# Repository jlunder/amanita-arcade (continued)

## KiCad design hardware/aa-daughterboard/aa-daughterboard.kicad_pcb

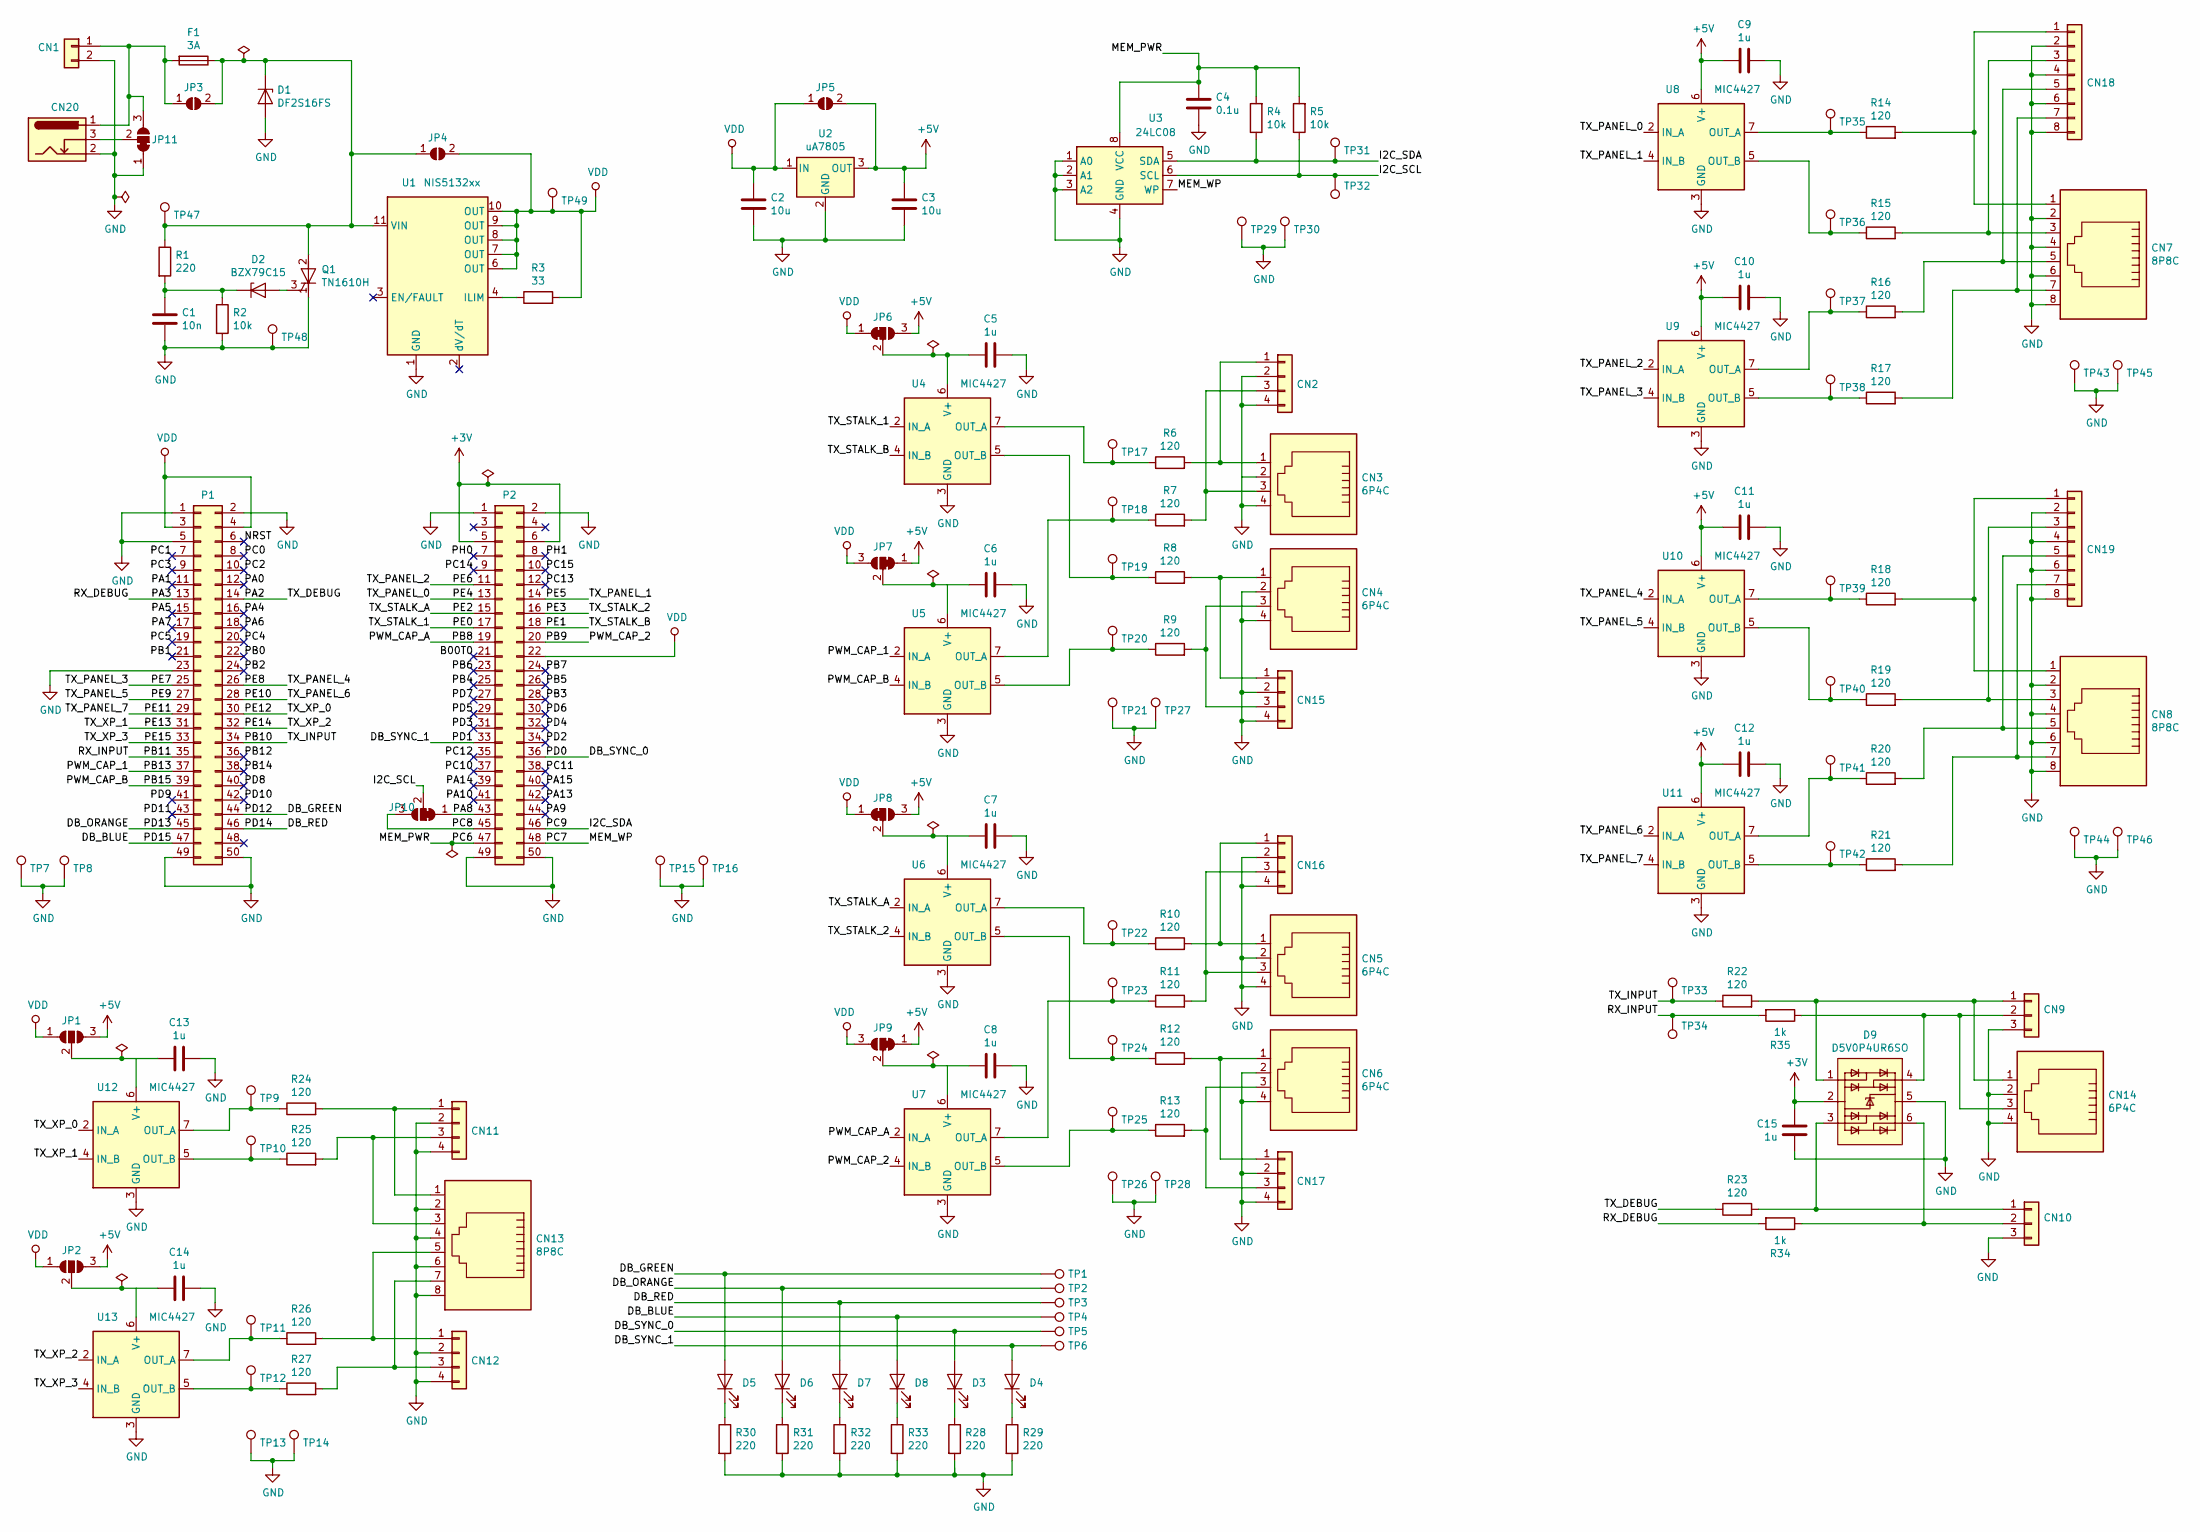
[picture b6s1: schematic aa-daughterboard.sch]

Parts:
C1: 10n; C_0603_1608Metric
C2, C3: 10u; C_0805_2012Metric
C4: 0.1u; C_0603_1608Metric
C5, C6, C7, C8, C9, C10, C11, C12, C13, C14, C15: 1u; C_0805_2012Metric
CN1: Conn_01x02; SolderWirePad_1x02_P7.62mm_Drill2.5mm
CN2, CN11, CN12, CN15, CN16, CN17: Conn_01x04; PinHeader_1x04_P2.54mm_Vertical
CN3, CN4, CN5, CN6, CN14: 6P4C; RJ25_Amphenol_90520
CN7, CN8, CN13: 8P8C; RJ25_Amphenol_69255
CN9, CN10: Conn_01x03; PinHeader_1x03_P2.54mm_Vertical
CN18, CN19: Conn_01x08; PinHeader_1x08_P2.54mm_Vertical
CN20: Barrel_Jack; BarrelJack_Horizontal
D1: DF2S16FS; D_SOD-923
D2: BZX79C15; D_DO-35_SOD27_P7.62mm_Horizontal
D3, D4, D5, D6, D7, D8: LED; LED_0603_1608Metric
D9: D5V0P4UR6SO; SOT-23-6
F1: 3A; Fuseholder_Clip_5x20_Bel_FC-211-22
JP1, JP2: SolderJumper_3_Open; SolderJumper-3_P1.3mm_Open_RoundedPad1.0x1.5mm
JP3, JP4, JP5: SolderJumper_2_Open; SolderJumper-2_P1.3mm_Open_RoundedPad1.0x1.5mm
JP6, JP7, JP8, JP9, JP10, JP11: SolderJumper_3_Bridged12; SolderJumper-3_P1.3mm_Bridged2Bar12_RoundedPad1.0x1.5mm
P1, P2: Conn_02x25_Odd_Even; PinSocket_2x25_P2.54mm_Vertical
Q1: TN1610H; TO-220-3_Horizontal_TabDown
R1, R28, R29, R30, R31, R32, R33: 220; R_0603_1608Metric
R2, R4, R5: 10k; R_0603_1608Metric
R3: 33; R_0603_1608Metric
R6, R7, R8, R9, R10, R11, R12, R13, R14, R15, R16, R17, R18, R19, R20, R21, R24, R25, R26, R27: 120; R_1210_3225Metric
R22, R23: 120; R_0603_1608Metric
R34, R35: 1k; R_0603_1608Metric
TP1, TP2, TP3, TP4, TP5, TP6, TP7, TP8, TP9, TP10, TP11, TP12, TP13, TP14, TP15, TP16, TP17, TP18, TP19, TP20, TP21, TP22, TP23, TP24, TP25, TP26, TP27, TP28, TP29, TP30, TP31, TP32, TP33, TP34, TP35, TP36, TP37, TP38, TP39, TP40, TP41, TP42, TP43, TP44, TP45, TP46, TP47, TP48, TP49: TestPoint; TestPoint_THTPad_D1.0mm_Drill0.5mm
U1: NIS5132xx; DFN-10-1EP_3x3mm_P0.5mm_EP1.75x2.7mm
U2: uA7805; TO-220-3_Vertical
U3: 24LC08; DIP-8_W7.62mm_Socket
U4, U5, U6, U7, U8, U9, U10, U11, U12, U13: MIC4427; SOIC-8-1EP_3.9x4.9mm_P1.27mm_EP2.35x2.35mm

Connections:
+3V: C15.1, D9.2 (A), P2.5, P2.6
+5V: C3.1, C9.1, C10.1, C11.1, C12.1, JP1.3 (B), JP2.3 (B), JP5.2 (B), JP6.3 (B), JP7.1 (A), JP8.3 (B), JP9.1 (A), U2.3 (OUT), U8.6 (V+), U9.6 (V+), U10.6 (V+), U11.6 (V+)
/B00T0: P2.21
/DB_BLUE: D8.2 (A), P1.47, TP4.1
/DB_GREEN: D5.2 (A), P1.44, TP1.1
/DB_ORANGE: D6.2 (A), P1.45, TP2.1
/DB_RED: D7.2 (A), P1.46, TP3.1
/DB_SYNC_0: D3.2 (A), P2.36, TP5.1
/DB_SYNC_1: D4.2 (A), P2.33, TP6.1
/I2C_SCL: JP10.2 (C), R5.1, TP32.1, U3.6 (SCL)
/I2C_SDA: P2.46, R4.1, TP31.1, U3.5 (SDA)
/MEM_PWR: C4.1, P2.47, R4.2, R5.2, U3.8 (VCC)
/MEM_WP: P2.48, U3.7 (WP)
/NRST: P1.6
/PA0: P1.12
/PA1: P1.11
/PA2: P1.14, R23.1
/PA3: P1.13, R34.2
/PA4: P1.16
/PA5: P1.15
/PA6: P1.18
/PA7: P1.17
/PA8: JP10.1 (A), P2.43
/PA9: P2.44
/PA10: P2.41
/PA13: P2.42
/PA14: P2.39
/PA15: P2.40
/PB0: P1.22
/PB1: P1.21
/PB2: P1.24
/PB3: P2.28
/PB4: P2.25
/PB5: P2.26
/PB6: P2.23
/PB7: P2.24
/PB8: P2.19, U7.2 (IN_A)
/PB9: P2.20, U7.4 (IN_B)
/PB10: P1.34, R22.1, TP33.1
/PB11: P1.35, R35.2, TP34.1
/PB12: P1.36
/PB13: P1.37, U5.2 (IN_A)
/PB14: P1.38
/PB15: P1.39, U5.4 (IN_B)
/PC0: P1.8
/PC1: P1.7
/PC2: P1.10
/PC3: P1.9
/PC4: P1.20
/PC5: P1.19
/PC8: JP10.3 (B), P2.45
/PC10: P2.37
/PC11: P2.38
/PC12: P2.35
/PC13: P2.12
/PC14: P2.9
/PC15: P2.10
/PD2: P2.34
/PD3: P2.31
/PD4: P2.32
/PD5: P2.29
/PD6: P2.30
/PD7: P2.27
/PD8: P1.40
/PD9: P1.41
/PD10: P1.42
/PD11: P1.43
/PE0: P2.17, U4.2 (IN_A)
/PE1: P2.18, U4.4 (IN_B)
/PE2: P2.15, U6.2 (IN_A)
/PE3: P2.16, U6.4 (IN_B)
/PE4: P2.13, U8.2 (IN_A)
/PE5: P2.14, U8.4 (IN_B)
/PE6: P2.11, U9.2 (IN_A)
/PE7: P1.25, U9.4 (IN_B)
/PE8: P1.26, U10.2 (IN_A)
/PE9: P1.27, U10.4 (IN_B)
/PE10: P1.28, U11.2 (IN_A)
/PE11: P1.29, U11.4 (IN_B)
/PE12: P1.30, U12.2 (IN_A)
/PE13: P1.31, U12.4 (IN_B)
/PE14: P1.32, U13.2 (IN_A)
/PE15: P1.33, U13.4 (IN_B)
/PH0: P2.7
/PH1: P2.8
GND: C1.2, C2.2, C3.2, C4.2, C5.2, C6.2, C7.2, C8.2, C9.2, C10.2, C11.2, C12.2, C13.2, C14.2, C15.2, CN1.2, CN2.2, CN2.4, CN3.2, CN3.4, CN4.2, CN4.4, CN5.2, CN5.4, CN6.2, CN6.4, CN7.2, CN7.4, CN7.6, CN7.8, CN8.2, CN8.4, CN8.6, CN8.8, CN9.3, CN10.3, CN11.2, CN11.4, CN12.2, CN12.4, CN13.2, CN13.4, CN13.6, CN13.8, CN14.2, CN14.4, CN15.2, CN15.4, CN16.2, CN16.4, CN17.2, CN17.4, CN18.2, CN18.4, CN18.6, CN18.8, CN19.2, CN19.4, CN19.6, CN19.8, CN20.2, D1.2 (A), D9.5 (K), JP11.1 (A), P1.1, P1.2, P1.5, P1.23, P1.49, P1.50, P2.1, P2.2, P2.49, P2.50, Q1.1 (K), R2.2, R28.2, R29.2, R30.2, R31.2, R32.2, R33.2, TP7.1, TP8.1, TP13.1, TP14.1, TP15.1, TP16.1, TP21.1, TP26.1, TP27.1, TP28.1, TP29.1, TP30.1, TP43.1, TP44.1, TP45.1, TP46.1, TP48.1, U1.1 (GND), U2.2 (GND), U3.1 (A0), U3.2 (A1), U3.3 (A2), U3.4 (GND), U4.3 (GND), U5.3 (GND), U6.3 (GND), U7.3 (GND), U8.3 (GND), U9.3 (GND), U10.3 (GND), U11.3 (GND), U12.3 (GND), U13.3 (GND)
unnamed: C1.1, D2.1 (K), R1.2, R2.1
unnamed: C5.1, JP6.2 (C), U4.6 (V+)
unnamed: C6.1, JP7.2 (C), U5.6 (V+)
unnamed: C7.1, JP8.2 (C), U6.6 (V+)
unnamed: C8.1, JP9.2 (C), U7.6 (V+)
unnamed: C13.1, JP1.2 (C), U12.6 (V+)
unnamed: C14.1, JP2.2 (C), U13.6 (V+)
unnamed: CN1.1, CN20.1, F1.2, JP3.1 (A), JP11.3 (B)
unnamed: CN2.1, CN3.1, R6.2
unnamed: CN2.3, CN3.3, R7.2
unnamed: CN10.1, D9.3 (K), R23.2
unnamed: CN10.2, D9.6 (K), R34.1
unnamed: CN11.1, CN13.1, R24.2
unnamed: CN11.3, CN13.3, R25.2
unnamed: CN12.1, CN13.5, R26.2
unnamed: CN12.3, CN13.7, R27.2
unnamed: CN9.1, CN14.1, D9.1 (K), R22.2
unnamed: CN9.2, CN14.3, D9.4 (K), R35.1
unnamed: CN4.1, CN15.1, R8.2
unnamed: CN4.3, CN15.3, R9.2
unnamed: CN5.1, CN16.1, R10.2
unnamed: CN5.3, CN16.3, R11.2
unnamed: CN6.1, CN17.1, R12.2
unnamed: CN6.3, CN17.3, R13.2
unnamed: CN7.1, CN18.1, R14.2
unnamed: CN7.3, CN18.3, R15.2
unnamed: CN7.5, CN18.5, R16.2
unnamed: CN7.7, CN18.7, R17.2
unnamed: CN8.1, CN19.1, R18.2
unnamed: CN8.3, CN19.3, R19.2
unnamed: CN8.5, CN19.5, R20.2
unnamed: CN8.7, CN19.7, R21.2
unnamed: CN20.3, JP11.2 (C)
unnamed: D1.1 (K), F1.1, JP3.2 (B), JP4.1 (A), Q1.2 (A), R1.1, TP47.1, U1.11 (VIN)
unnamed: D2.2 (A), Q1.3 (G)
unnamed: D3.1 (K), R28.1
unnamed: D4.1 (K), R29.1
unnamed: D5.1 (K), R30.1
unnamed: D6.1 (K), R31.1
unnamed: D7.1 (K), R32.1
unnamed: D8.1 (K), R33.1
unnamed: R3.1, U1.4 (ILIM)
unnamed: R6.1, TP17.1, U4.7 (OUT_A)
unnamed: R7.1, TP18.1, U5.7 (OUT_A)
unnamed: R8.1, TP19.1, U4.5 (OUT_B)
unnamed: R9.1, TP20.1, U5.5 (OUT_B)
unnamed: R10.1, TP22.1, U6.7 (OUT_A)
unnamed: R11.1, TP23.1, U7.7 (OUT_A)
unnamed: R12.1, TP24.1, U6.5 (OUT_B)
unnamed: R13.1, TP25.1, U7.5 (OUT_B)
unnamed: R14.1, TP35.1, U8.7 (OUT_A)
unnamed: R15.1, TP36.1, U8.5 (OUT_B)
unnamed: R16.1, TP37.1, U9.7 (OUT_A)
unnamed: R17.1, TP38.1, U9.5 (OUT_B)
unnamed: R18.1, TP39.1, U10.7 (OUT_A)
unnamed: R19.1, TP40.1, U10.5 (OUT_B)
unnamed: R20.1, TP41.1, U11.7 (OUT_A)
unnamed: R21.1, TP42.1, U11.5 (OUT_B)
unnamed: R24.1, TP9.1, U12.7 (OUT_A)
unnamed: R25.1, TP10.1, U12.5 (OUT_B)
unnamed: R26.1, TP11.1, U13.7 (OUT_A)
unnamed: R27.1, TP12.1, U13.5 (OUT_B)
VDD: C2.1, JP1.1 (A), JP2.1 (A), JP4.2 (B), JP5.1 (A), JP6.1 (A), JP7.3 (B), JP8.1 (A), JP9.3 (B), P1.3, P1.4, P2.22, R3.2, TP49.1, U1.6 (OUT), U1.7 (OUT), U1.8 (OUT), U1.9 (OUT), U1.10 (OUT), U2.1 (IN)

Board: 4 copper layers, 156 parts (1 on the bottom side), 102 nets, no tracks yet.

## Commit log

2015-10-15 LED blinky test.
2015-10-17 Some kinda audio output when I don't use DMA?
2015-10-17 DMA circular buffer audio works! Yay
2015-10-17 Audio data
2015-10-17 Heartbeat sound fully working!
2015-10-18 Final for the party!
2016-04-16 Rename to Amanita Arcade, begin refactor/cleanup
2016-05-24 Begin integrating synth stuff from rotterbox
2016-05-24 MPR121 code
2016-06-02 Get touch working with MPR121 sensors
2016-06-04 Sketch out game logic, UART hardware implementation
2016-06-05 Add a couple high frequency timers.
2016-06-07 Add hardware support for WS2811 output via I2S -- fix problem with I2S clock generation (??? I think? How did this ever work with the CS43L22 though?)
2016-06-08 Yay basic output seems to basically work!
2016-06-09 Fix color order in test pattern, bit order in output code
2016-06-11 Refactor code out of ugly giant main.c and into submodules
2016-06-18 Build out skeleton of game and animation/audio code
2016-06-28 Decluttering, start implementing light control
2016-07-01 Add timer support to HW lib, switch to bitbanged LED output.
2016-07-03 Implement first pass light compositing
2016-07-04 Fix cycle play bugs.
2016-07-09 Minor changes to match festival hardware
2017-05-18 Add GitEye .project exclusion
2017-06-23 Add new mbed rewrite of Amanita Arcade. Wish me luck
2017-06-23 Basic skeleton, some utilities here
2017-06-23 First pass input, much framework
2017-06-24 Debug test controller input.
2017-06-25 Implement algorithm to pack light data for output via serial port (!!)
2017-06-25 First working version of WS2812 (serial) drive
2017-06-25 First pass of WS2812 output -- output works, seems stable over long(ish) cable runs.
2017-06-26 Beginning implementation of lights animation framework.
2017-06-27 First crack at new animation system
2017-07-07 Add separate firmware for the controls controller
2017-07-07 Fix pin assignment
2017-07-07 First pass of actual (WS2812) output ordering/encoding
2017-07-07 Rename aa-test-1 to aa-main 'cause it's the real deal now
2017-07-07 Straighten out composite step slightly
2017-07-08 Much bugfixing, implement lights on button press
2017-07-08 Final thing! Implemented game logic.
2017-08-06 Remove old, stale source
2017-08-06 Initial values were causing the controller to think all buttons were held down constantly forever if PS2 controller not plugged in on boot.
2017-08-06 Fix rendering bugs, change gameplay to use the first button press as start of sequence
2018-06-20 Improve efficiency of output() by using work to delay instead of __NOP()
2018-06-20 Add explicit optimization/memory barrier control to output() as future-proofing
2018-06-24 Tweak lights output to show scoreboard at 13% intensity, show actually the output in the buffer rather than a test pattern
2018-07-01 Panel font render test
2018-07-02 Clean up some of the LED output code
2018-07-02 Font, cursor test
2018-07-02 Font gradients, to improve legibility
2018-07-03 Add invert option to font rendering for the cursor
2018-07-03 Add debug background to output code, adjust timing slightly
2018-07-03 Separate color reorder for panel and stalks... that was a confusing color problem
2018-07-04 Refactor pool system, add (ugh) templates to make it easier to add animators
2018-07-07 Refactor a bunch of draw code, implement scrolling text for instructions
2018-07-08 Refactor/rewrite a bunch of stuff! Also implement vis for scoreboard.
2018-07-29 Add VS Code .gitignore, make project work on latest Platform.IO (now it offers mbed upload for STM32F4Discovery which is not helpful)
2018-07-29 Don't mess with the JTAG lines (it was wigging OpenOCD out)
2018-07-29 Make a best effort to output message from asserts that happen during static init
2018-07-29 Cleanup, improve formatting consistency, VS Code Platform.IO stuff
2018-07-29 Improve debug serial on-demand init a little more elegantly so we can log messages/asserts during static init in a general way
2018-07-29 Fix broken uptime(), frame timing code
2018-07-29 Fix copy in comment
2018-07-30 Implement watchdog timer!
2018-07-30 Not sure why vscode decided to change these settings but sure
2018-07-30 Add input via debug_ser, log game state via vis, adjust vis design slightly
2018-08-01 Fix timer bugs, add debug serial input simulation, reimplement game logic with a modular state machine, fix spurious assert in lights
2018-08-04 Tweak glow/press animations
2018-08-06 Fix issues with transitions, make colors brace-initializable, rationalize draw function naming, improve logo texture, tweak viz
2018-08-07 Tweak animations, etc.
2018-08-07 Fix small bug with endgame handling
2018-08-07 Narrow font for readability, tweak animations
2018-08-27 Implement bitbang I2C for EEPROM
2018-10-15 Consolidate source data, organize
2019-01-03 Post-shambs development (used at Lumiere)
2019-04-19 Current LVDS/RS422 project -- pretty much ready for layout
2019-04-20 First run at aa-daughterboard (current loop version), plus WIP
2019-04-22 Rough grouping of components done
2019-04-23 Add STM32 symbols... I don't think I have this right yet
2019-04-23 Name differential pairs, convert inconvenient 1x8 connectors to 2x4
2019-04-23 Clear out autosaves/junk
2019-04-23 Add gitignore to prevent junk from coming back
2019-05-04 Routed, labeling done pending double check
2019-05-05 Tweaks and labeling changes
2019-05-18 Add new projects for remaining boards, remove cruft
2019-05-18 Updates to schematic and layout -- remove test points, add jumpers, iterate layout
2019-05-22 Latest stalk receiver design -- many tweaks, layout V0 probably done
2019-05-22 Add BOM used for order, todos
2019-05-23 Updated notes
2019-05-24 Implement todos
2019-05-25 Finish implementing daughterboard todos, except BOM on silkscreen, update library tables.
2019-06-02 More updates to daughterboard, begin panel receiver layout
2019-06-02 Update todos
2019-06-04 Add power distro board, resolve some todos, finish a coherent layout of the panel receiver
2019-06-08 Update to use a shared schematic component/footprint library
2019-06-09 Design, lay out power protection/distribution board
2019-06-10 Fix bad test point label
2019-06-10 Fix spurious assert fail, tidy
2019-06-10 WIP work on I2C
2019-06-10 Exclude .vscode/ipch
2019-06-10 More TODOs
2019-06-16 Substantial rework of system, new layouts done for daughterboard, power, stalk receiver
2019-06-16 Renumber and duplicate layout for panel receiver -- layout not complete
2019-06-17 Placement of components on panel receiver board, routing TBD
2019-06-20 Second rount almost ready, less fiducials
2019-06-22 Final designs and actual sent gerbers for first for-real run
2019-06-24 Second run of PCBs for Amanita Arcade
2019-07-01 Sent to manufacturing
2019-07-27 Remove unused audio files left over from embrace-heart-...
2019-08-07 Minor board updates to fix issues discovered during build
2019-08-07 Add STM32 port of input controller
2019-08-07 Remove old Arduino code for input controller
2019-08-07 Disable extra timing info for production version
2019-08-08 Fix button order
2019-08-08 Fix silkscreen for stalk connectors
2019-08-19 Fix label ordering to match board
2019-08-19 Reorganize code, fix bugs -- input board recovers properly now
2019-08-19 Add watchdog timer to input board
2019-09-05 Add initial hi score implementation, add debug interface, move game vis and hi score stuff to their own files, switch to C++17
2019-09-05 First working implementation of hi score list
2019-09-10 Switch color to 8:8:8:8 fixed point, add render debug, fix stuck transition times
2019-09-23 Rework lights output to use DMA -- hopefully this won't be so finicky
2019-09-23 Back to 40fps (we could probably do 50 or 60 but for the unbuffered serial log)
2019-11-16 Playing around with board support for the F411
2022-07-01 Update deprecated config vars
2022-07-01 Update deprecated wait_ms to wait_us
2022-07-01 Fix DMA output to be more reliable (no sparklies!)
2022-07-01 Return to old pins, USART3 and I2C3 don't conflict
2022-07-03 Switch to RTOS build of mbed for aa-main
2022-07-03 Streamline input firmware, fix reset issue
2022-07-06 Tidy includes
2022-07-06 Improve RNG, fix input thread, double-buffer lights
